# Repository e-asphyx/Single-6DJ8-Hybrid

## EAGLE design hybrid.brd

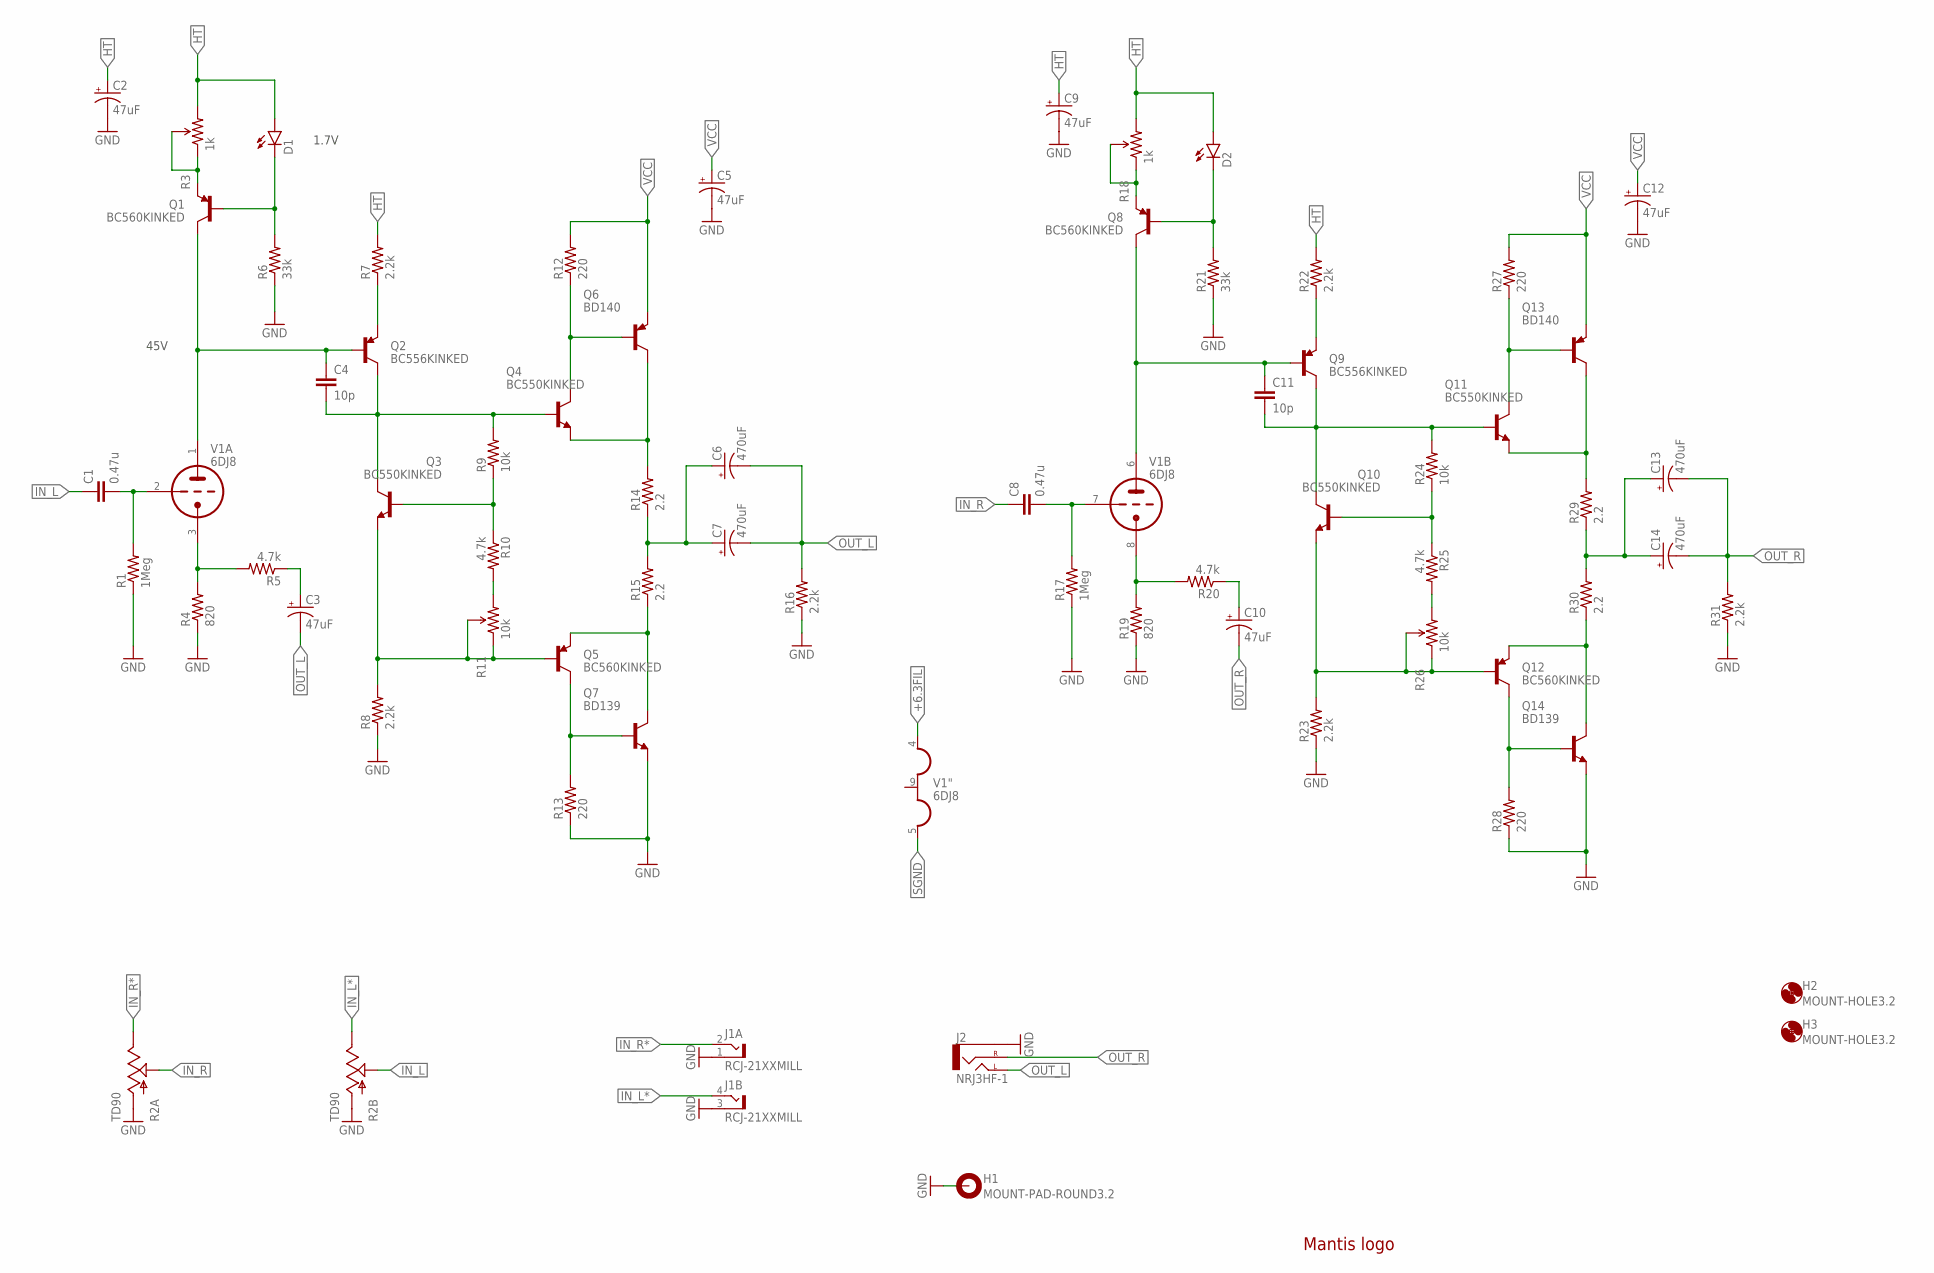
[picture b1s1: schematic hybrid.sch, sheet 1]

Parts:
C1, C8: 0.47u; C5B3.5
C2, C3, C5, C9, C10, C12: 47uF; CPOL-RADIAL-8/3.5
C4, C11: 10p; CAP-PTH-SMALL
C6, C7, C13, C14: 470uF; CPOL-RADIAL-12/5
D1, D2: LED3MM
H1: MOUNT-PAD-ROUND3.2; 3,2-PAD
H2, H3: MOUNT-HOLE3.2; 3,2
J1: RCJ-21XXMILL; RCJ-21-MILL
J2: NRJ3HF-1; NRJ3HF
LOGO1: LOGO-MANTIS
Q1, Q5, Q8, Q12: BC560KINKED; TO92-BENT
Q2, Q9: BC556KINKED; TO92-BENT
Q3, Q4, Q10, Q11: BC550KINKED; TO92-BENT
Q6, Q13: BD140; TO126
Q7, Q14: BD139; TO126
R1, R17: 1Meg; AXIAL-0.4
R2: TD90; PTD902
R3, R18: 1k; 3362U-2
R4, R19: 820; AXIAL-0.4
R5, R10, R20, R25: 4.7k; AXIAL-0.4
R6, R21: 33k; AXIAL-0.4
R7, R8, R16, R22, R23, R31: 2.2k; AXIAL-0.4
R9, R24: 10k; AXIAL-0.4
R11, R26: 10k; 3362U-2
R12, R13, R27, R28: 220; AXIAL-0.4
R14, R15, R29, R30: 2.2; AXIAL-0.5
V1: 6DJ8; NOVAL

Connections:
+6.3FIL: V1.4 (H1); also elsewhere on the board
CAT_L: R4.P$2 (2), R5.P$2 (2), V1.3 (TK)
CAT_R: R19.P$2 (2), R20.P$2 (2), V1.8 (TK)
FB_L: C6.+, C7.+, R14.P$1 (1), R15.P$2 (2)
FB_R: C13.+, C14.+, R29.P$1 (1), R30.P$2 (2)
GND: C2.2 (-), C5.2 (-), C9.2 (-), C12.2 (-), H1.B3,2, J1.1 (S), J1.3 (S), J2.S (SLEEVE), Q7.1 (E), Q14.1 (E), R1.P$1 (1), R2.R1.1 (A), R2.R2.1 (A), R4.P$1 (1), R6.P$1 (1), R8.P$1 (1), R13.P$1 (1), R16.P$1 (1), R17.P$1 (1), R19.P$1 (1), R21.P$1 (1), R23.P$1 (1), R28.P$1 (1), R31.P$1 (1); also elsewhere on the board
HT: C2.1 (+), C9.1 (+), D1.A, D2.A, R3.3 (CW), R7.P$2 (2), R18.3 (CW), R22.P$2 (2); also elsewhere on the board
IN_L: C1.1, R2.R2.2 (S)
IN_L*: J1.4 (T), R2.R2.3 (E)
IN_R: C8.1, R2.R1.2 (S)
IN_R*: J1.2 (T), R2.R1.3 (E)
unnamed: Q1.3 (E), R3.1 (CCW), R3.2 (WIPER)
unnamed: D1.K (C), Q1.2 (B), R6.P$2 (2)
unnamed: C3.1 (+), R5.P$1 (1)
unnamed: Q2.3 (E), R7.P$1 (1)
unnamed: C4.2, Q2.1 (C), Q3.1 (C), Q4.2 (B), R9.P$2 (2)
unnamed: Q3.2 (B), R9.P$1 (1), R10.P$1 (1)
unnamed: C1.2, R1.P$2 (2), V1.2 (TG)
unnamed: R10.P$2 (2), R11.3 (CW)
unnamed: Q4.3 (E), Q6.2 (C), R14.P$2 (2)
unnamed: Q3.3 (E), Q5.2 (B), R8.P$2 (2), R11.1 (CCW), R11.2 (WIPER)
unnamed: Q5.3 (E), Q7.2 (C), R15.P$1 (1)
unnamed: Q4.1 (C), Q6.3 (B), R12.P$1 (1)
unnamed: Q5.1 (C), Q7.3 (B), R13.P$2 (2)
unnamed: Q8.3 (E), R18.1 (CCW), R18.2 (WIPER)
unnamed: D2.K (C), Q8.2 (B), R21.P$2 (2)
unnamed: C8.2, R17.P$2 (2), V1.7 (TG)
unnamed: C10.1 (+), R20.P$1 (1)
unnamed: Q9.3 (E), R22.P$1 (1)
unnamed: C11.2, Q9.1 (C), Q10.1 (C), Q11.2 (B), R24.P$2 (2)
unnamed: Q10.2 (B), R24.P$1 (1), R25.P$1 (1)
unnamed: R25.P$2 (2), R26.3 (CW)
unnamed: Q10.3 (E), Q12.2 (B), R23.P$2 (2), R26.1 (CCW), R26.2 (WIPER)
unnamed: Q11.3 (E), Q13.2 (C), R29.P$2 (2)
unnamed: Q12.3 (E), Q14.2 (C), R30.P$1 (1)
unnamed: Q11.1 (C), Q13.3 (B), R27.P$1 (1)
unnamed: Q12.1 (C), Q14.3 (B), R28.P$2 (2)
OUT_L: C3.2 (-), C6.-, C7.-, J2.T (LEFT), R16.P$2 (2)
OUT_R: C10.2 (-), C13.-, C14.-, J2.R (RIGHT), R31.P$2 (2)
PL_L: C4.1, Q1.1 (C), Q2.2 (B), V1.1 (TA)
PL_R: C11.1, Q8.1 (C), Q9.2 (B), V1.6 (TA)
SGND: V1.5 (H3); also elsewhere on the board
VCC: C5.1 (+), C12.1 (+), Q6.1 (E), Q13.1 (E), R12.P$2 (2), R27.P$2 (2); also elsewhere on the board

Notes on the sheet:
1.7V
45V

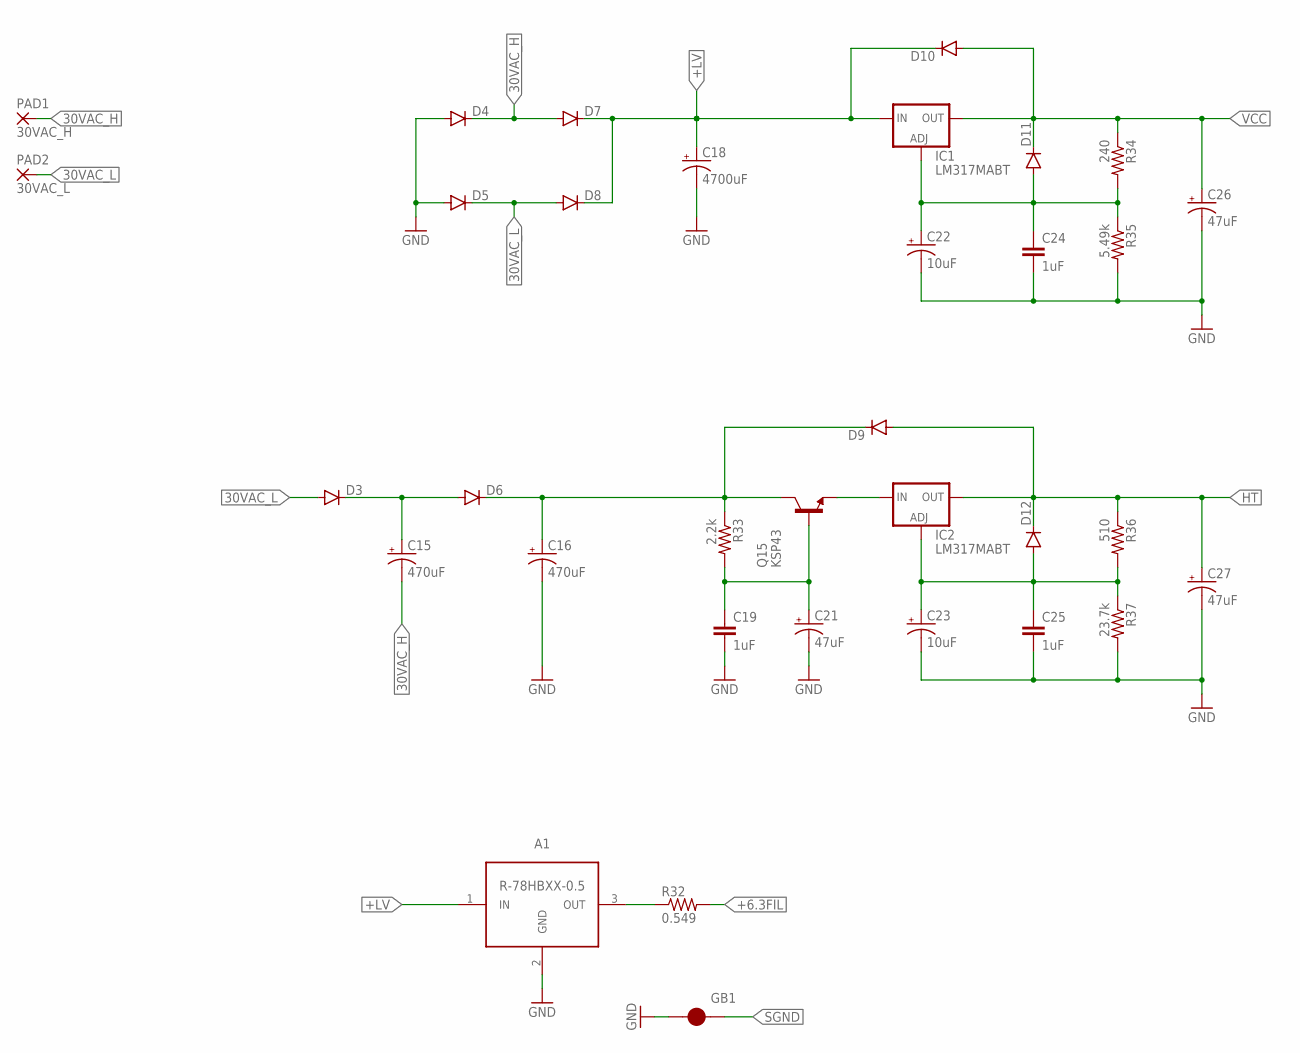
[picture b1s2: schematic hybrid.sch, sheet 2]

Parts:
A1: R-78HBXX-0.5; R-78HB
C15, C16: 470uF; CPOL-RADIAL-16/7.5
C18: 4700uF; CPOL-RADIAL-22/10
C19, C24, C25: 1uF; CAP-PTH-SMALL
C21: 47uF; CPOL-RADIAL-12/5
C22: 10uF; CPOL-RADIAL-5/2.5
C23: 10uF; CPOL-RADIAL-6.5/2.5
C26, C27: 47uF; CPOL-RADIAL-8/3.5
D3, D4, D5, D6, D7, D8, D9, D10, D11, D12: DIODEPTH; DIODE-1N4001
GB1: COPPER-BRIDGESM; COPPER-BRIDGE-SM
IC1, IC2: LM317MABT; TO220L1
PAD1: 30VAC_H; 3,81/1,4
PAD2: 30VAC_L; 3,81/1,4
Q15: KSP43; TO-92
R32: 0.549; AXIAL-0.5
R33: 2.2k; AXIAL-0.4
R34: 240; AXIAL-0.4
R35: 5.49k; AXIAL-0.4
R36: 510; AXIAL-0.4
R37: 23.7k; AXIAL-0.4

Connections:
30VAC_H: C15.2 (-), D4.C, D7.A, PAD1.1
30VAC_L: D3.A, D5.C, D8.A, PAD2.1
+6.3FIL: R32.P$2 (2); also elsewhere on the board
+LV: A1.1 (IN), C18.1 (+), D7.C, D8.C, D10.C, IC1.3 (IN)
GND: A1.2 (GND), C16.2 (-), C18.2 (-), C19.2, C21.-, C22.2 (-), C23.2 (-), C24.2, C25.2, C26.2 (-), C27.2 (-), D4.A, D5.A, GB1.1, R35.P$2 (2), R37.P$2 (2); also elsewhere on the board
HT: C27.1 (+), D9.A, D12.C, IC2.2 (OUT), R36.P$1 (1); also elsewhere on the board
unnamed: C22.1 (+), C24.1, D11.A, IC1.1 (ADJ), R34.P$2 (2), R35.P$1 (1)
unnamed: C15.1 (+), D3.C, D6.A
unnamed: A1.3 (OUT), R32.P$1 (1)
unnamed: C16.1 (+), D6.C, D9.C, Q15.3 (C), R33.P$1 (1)
unnamed: C19.1, C21.+, Q15.2 (B), R33.P$2 (2)
unnamed: C23.1 (+), C25.1, D12.A, IC2.1 (ADJ), R36.P$2 (2), R37.P$1 (1)
unnamed: IC2.3 (IN), Q15.1 (E)
SGND: GB1.2; also elsewhere on the board
VCC: C26.1 (+), D10.A, D11.C, IC1.2 (OUT), R34.P$1 (1); also elsewhere on the board

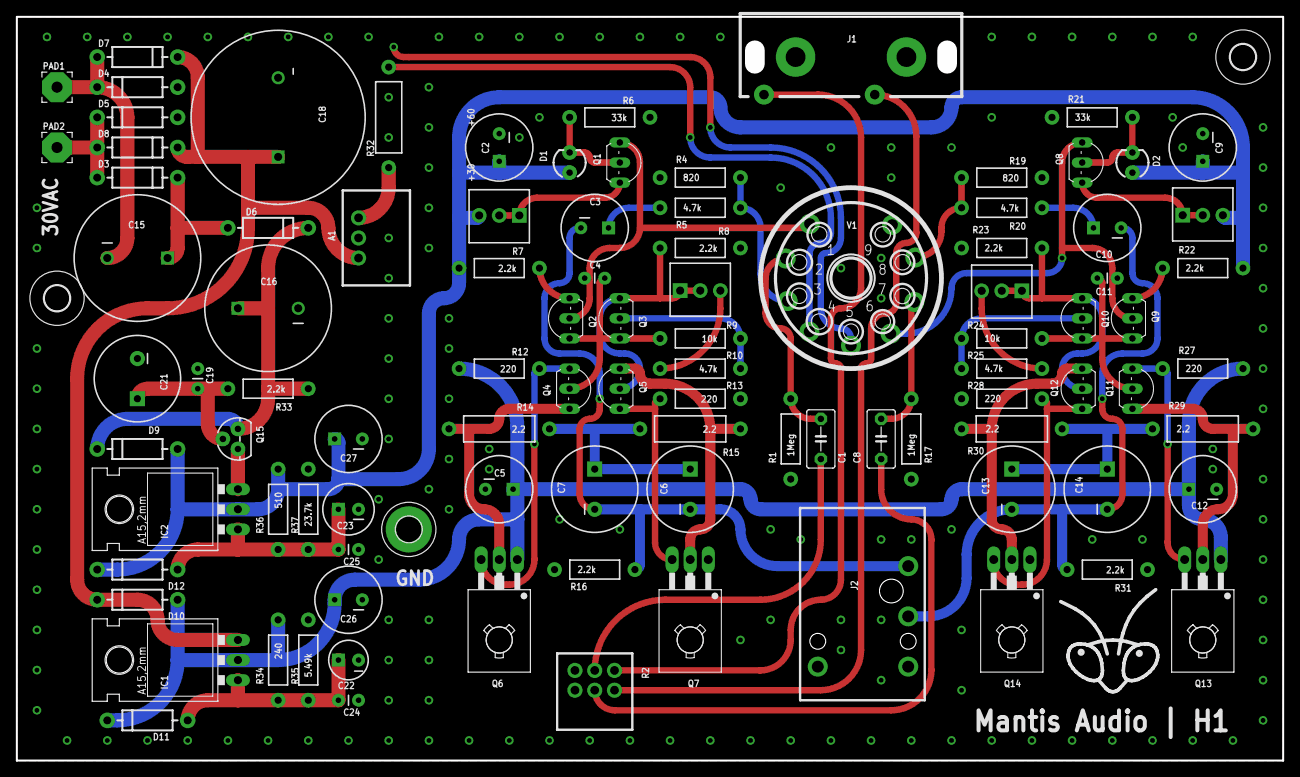
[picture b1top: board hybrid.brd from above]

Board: 2 copper layers, 157.8 x 91.7 mm, 102 parts (0 on the bottom side), 53 nets.

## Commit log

2016-11-02 Initial
2016-11-06 Mounting holes, caps layout
2016-11-18 Amp + PS on the same board. Rerouted from scratch
2016-11-24 Small fix
2017-01-19 PDF updated

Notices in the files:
parts and their libraries:
SparkFun-LED: Licensing: Creative Commons ShareAlike 4.0 International - https://creativecommons.org/licenses/by-sa/4.0
